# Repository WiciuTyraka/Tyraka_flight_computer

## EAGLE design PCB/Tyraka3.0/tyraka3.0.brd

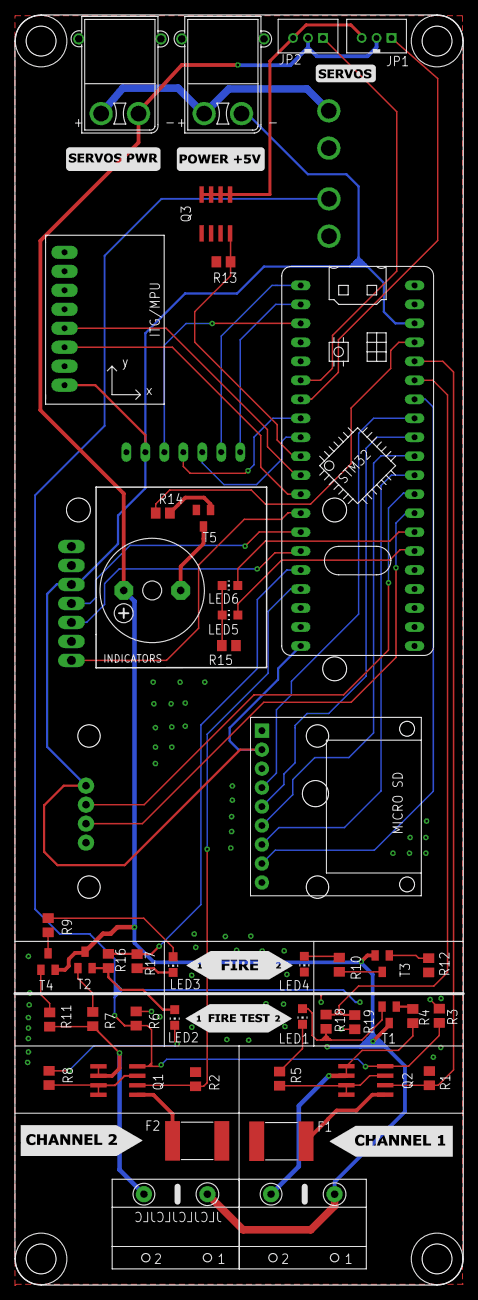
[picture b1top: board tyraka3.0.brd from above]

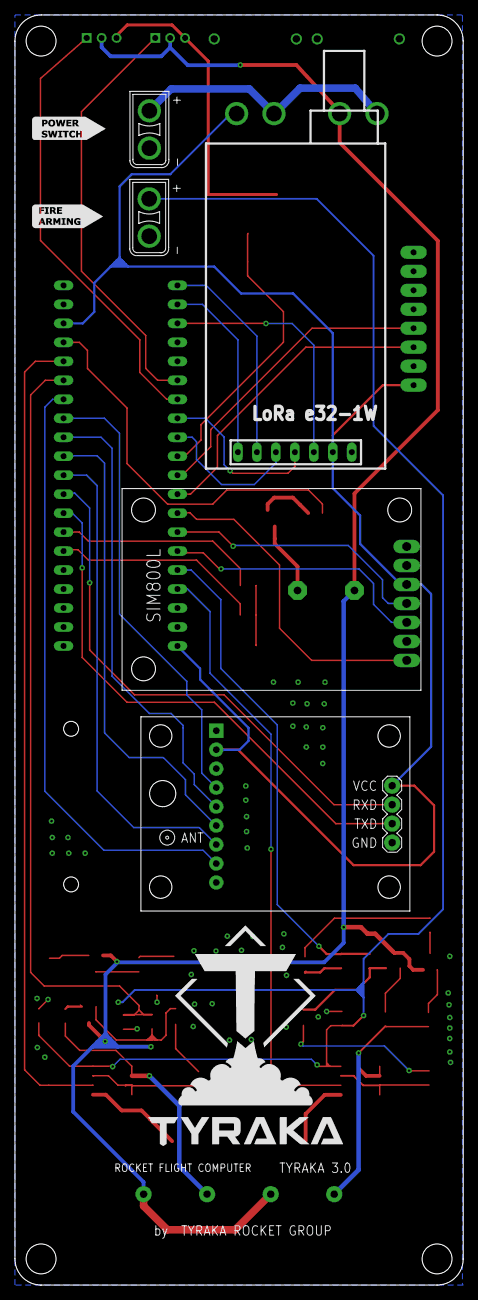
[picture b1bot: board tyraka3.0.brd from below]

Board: 2 copper layers, 60.0 x 170.0 mm, 49 parts (5 on the bottom side), 54 nets.

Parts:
F1, F2: 2920L030; 2920L
JP1, JP2: 3PIN; B3B-PH-K-S
LED1, LED2, LED3, LED4, LED5, LED6: CHIP-LED0805
Q1, Q2: IRF8313P; SO-08
Q3: SO-08
R1, R2, R3, R6: 33k; R0805
R4, R5, R7, R8, R9, R10, R14, R15, R16, R17, R18, R19: 1k; R0805
R11, R12, R13: 10k; R0805
SD1: MICRO_SD
SG1: F/CM12P
T1, T2: BC846; SOT23
T3, T4, T5: SOT23-BEC
U2: GY-521MPU6050; GY-521
U$1: SIM800L; SIP
U$2: LORA_E32
U$3: BLUE_PILL
U$4: GPS_TYRAKA; GPS-RECEIVER-NEO6M
U$5, U$6: XT30_MALE_90; XT60_MALE_90
U$7: 4X_ARK_8.5MM; 4XZLACZESRUBOWE
U$8, U$9: XT30UPB-M

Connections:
+3V3: SD1.P2, U2.VCC, U$1.3, U$2.VCC, U$3.3.3V1, U$3.3V3, U$4.VCC, U$6.P$2
AUX: U$2.AUX, U$3.PB14
BUZZER: R14.1, U$3.PB10
CD_SD: SD1.P8, U$3.PB0
CHANNEL_1: Q2.5, Q2.6, R4.2, U$7.P$2
CHANNEL_2: Q1.5, Q1.6, R7.2, R11.1, U$7.P$4
CLK: SD1.P6, U$3.PA5
CS_SD: SD1.P7, U$3.PA4
FIRE_CHANNEL_1_EN: Q2.2, R1.2, U$3.PB2
FIRE_CHANNEL_1_TEST: R18.2, R19.2, U$3.PB1
FIRE_CHANNEL_2_EN: Q1.2, R2.2, U$3.PB9
FIRE_CHANNEL_2_TEST: R16.2, R17.1, U$3.PB8
FIRE_CHANNEL_ARMING: Q1.4, Q2.4, R3.2, R6.2, U$8.P$1
GND: F1.2, F2.2, LED3.C, LED4.C, Q3.1, Q3.2, Q3.3, R1.1, R2.1, R3.1, R6.1, R13.1, R15.1, R17.2, R19.1, SD1.P1, T5.E, U2.GND, U$1.2, U$1.6, U$2.GND, U$3.GND, U$3.GND2, U$4.GND, U$8.P$2, U$9.P$2
LED1: LED5.A, U$3.PA0
LED2: LED6.A, U$3.PA1
M0: U$2.M0, U$3.PB13
M1: U$2.M1, U$3.PB12
MISO: SD1.P5, U$3.PA6
MOSI: SD1.P4, U$3.PA7
unnamed: F1.1, Q2.1
unnamed: F2.1, Q1.1
unnamed: Q2.3, Q2.7, Q2.8, R5.1
unnamed: Q1.3, Q1.7, Q1.8, R8.1
unnamed: LED1.C, R5.2
unnamed: SG1.-, T5.C
unnamed: LED2.C, R8.2
unnamed: R14.2, T5.B
unnamed: R4.1, T1.1
unnamed: R7.1, T2.1
unnamed: R12.2, T3.B
unnamed: R10.2, T3.C
unnamed: LED4.A, R10.1
unnamed: LED5.C, LED6.C, R15.2
unnamed: LED2.A, R16.1, T2.2
unnamed: R9.2, T4.C
unnamed: LED3.A, R9.1
unnamed: R11.2, T4.B
unnamed: JP1.3, JP2.3, Q3.5, Q3.6, Q3.7, Q3.8
unnamed: LED1.A, R18.1, T1.2
RST_SIM: U$1.7, U$3.PB5
RX_GPS: U$3.PA3, U$4.RX
RX_LORA: U$2.RX, U$3.PA12
RX_SIM: U$1.5, U$3.PB7
SCL: U2.SCL, U$3.PB4
SCREW_SWITCH_GND: U$5.P$1, U$6.P$1, U$9.P$1
SDA: U2.SDA, U$3.PB3
SERVO_1: JP2.1, U$3.PA9
SERVO_2: JP1.1, U$3.PA10
SERVO_PWR: Q3.4, R13.2, U$3.PA15
TX_GPS: U$3.PA2, U$4.TX
TX_LORA: U$2.TX, U$3.PA11
TX_SIM: U$1.4, U$3.PB6
V+: JP1.2, JP2.2, SG1.+, T1.3, T2.3, T3.E, T4.E, U$5.P$2, U$7.P$1, U$7.P$3

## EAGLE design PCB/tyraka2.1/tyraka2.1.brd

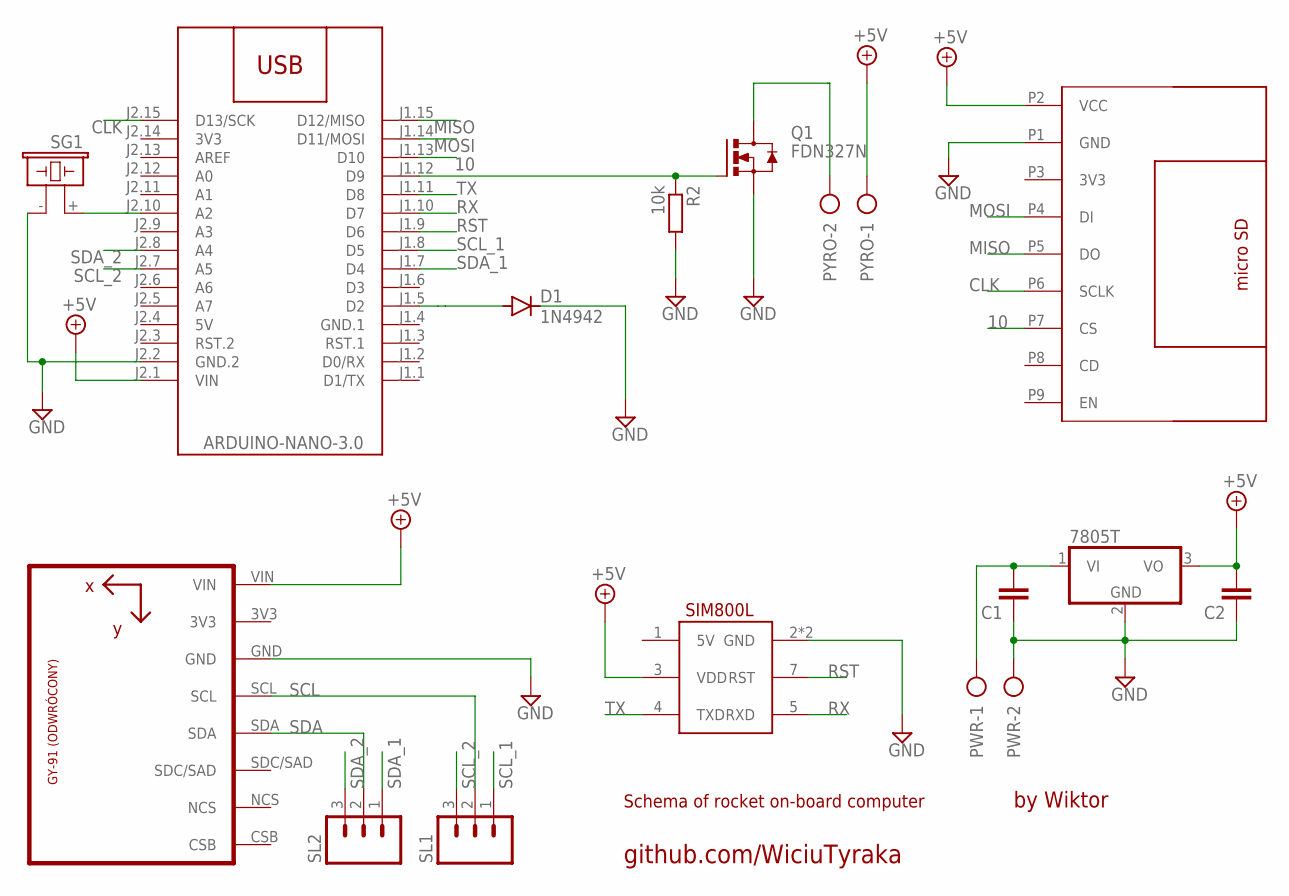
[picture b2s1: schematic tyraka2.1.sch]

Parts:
C1, C2: C2.5/4; C2.5-4
D1: 1N4942; DO41-10
IC2: 7805T; TO220H
M1: ARDUINO-NANO-3.0
PWR: AK500/2
PYRO: AK500/2
Q1: FDN327N; SOT23
R2: 10k; 0204/5
SD1: MICRO_SD
SG1: F/CM12P
SL1, SL2: M03; 03P
U1: GY-521MPU6050; GY-521
U$1: SIM800L; SIP

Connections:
3V3: M1.J2.14 (3V3)
5V: M1.J2.4 (5V)
10: M1.J1.13 (D10), SD1.P7 (CS)
+5V: C2.2, IC2.3 (VO), M1.J2.1 (VIN), PYRO.1, SD1.P2 (VCC), U1.VIN, U$1.3 (VDD)
CLK: M1.J2.15 (D13/SCK), SD1.P6 (SCLK)
GND: C1.1, C2.1, D1.C, IC2.2 (GND), M1.J2.2 (GND.2), PWR.2, Q1.2 (S), R2.2, SD1.P1 (GND), SG1.- (2), U1.GND, U$1.2 (GND), U$1.6 (GND)
GND.1: M1.J1.4 (GND.1)
MISO: M1.J1.15 (D12/MISO), SD1.P5 (DO)
MOSI: M1.J1.14 (D11/MOSI), SD1.P4 (DI)
unnamed: PYRO.2, Q1.3 (D)
unnamed: M1.J1.12 (D9), Q1.1 (G), R2.1
unnamed: D1.A, M1.J1.5 (D2)
unnamed: M1.J2.10 (A2), SG1.+ (1)
unnamed: C1.2, IC2.1 (VI), PWR.1
RST: M1.J1.9 (D6), U$1.7 (RST)
RX: M1.J1.10 (D7), U$1.5 (RXD)
SCL: SL1.2, U1.SCL
SCL_1: M1.J1.8 (D5), SL1.1
SCL_2: M1.J2.7 (A5), SL1.3
SDA: SL2.2, U1.SDA
SDA_1: M1.J1.7 (D4), SL2.1
SDA_2: M1.J2.8 (A4), SL2.3
TX: M1.J1.11 (D8), U$1.4 (TXD)

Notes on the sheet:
by Wiktor
Schema of rocket on-board computer
github.com/WiciuTyraka

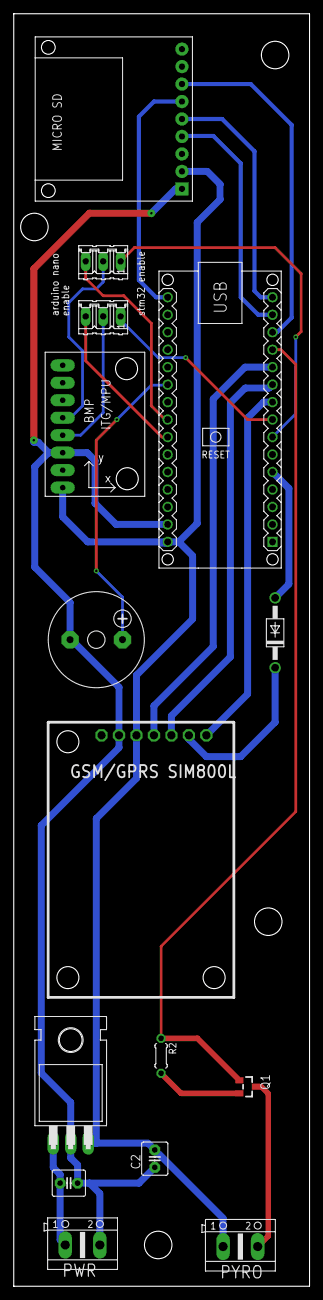
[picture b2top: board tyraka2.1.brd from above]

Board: 2 copper layers, 43.0 x 185.0 mm, 15 parts (0 on the bottom side), 20 nets.

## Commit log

2020-07-13 first_commit
    add tyraka 3.0
2020-07-19 adding library
    add scre terminal library
2020-07-19 improved tPlaces
    add fancy stuff to tPlaces and bPlaces
2020-07-19 last_Save
    last save
2020-07-20 add_few_features
    add_few_features to board like round corners and place for jlc signature
2020-07-25 swap 5 with 3v3
    add
    -3v3 swap with 5
    -add dzielniknapiecia
2020-07-26 dzielnik napiecia
    add dzielnik napiecia
    and few fixes

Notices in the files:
parts and their libraries:
ads1115: Released under the Creative Commons Attribution 4.0 International License: http://creativecommons.org/licenses/by/4.0
m-pad-2.1: License : GNU General Public License version 2 (see bottom)
